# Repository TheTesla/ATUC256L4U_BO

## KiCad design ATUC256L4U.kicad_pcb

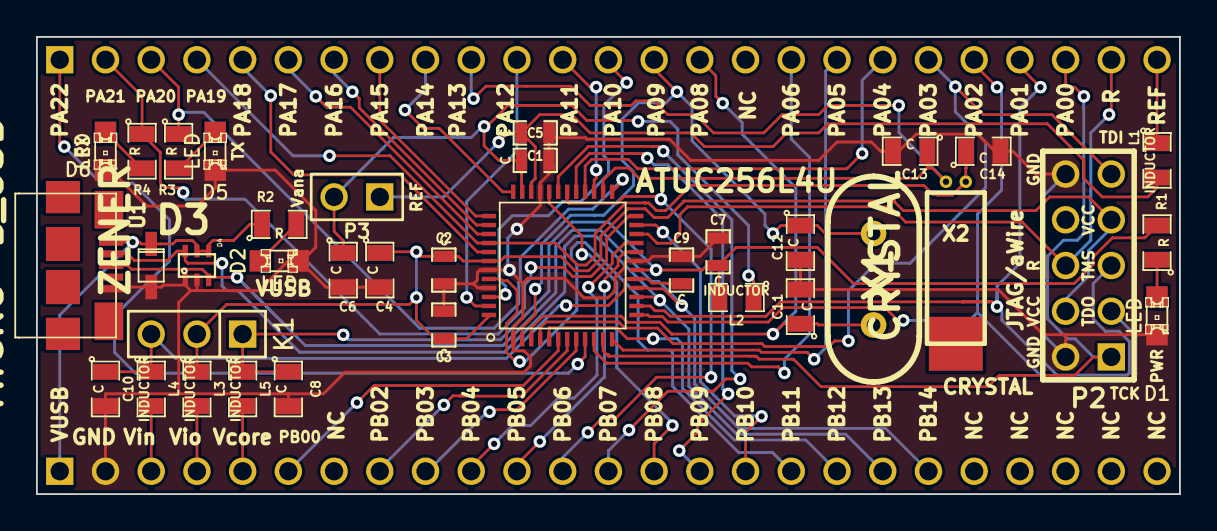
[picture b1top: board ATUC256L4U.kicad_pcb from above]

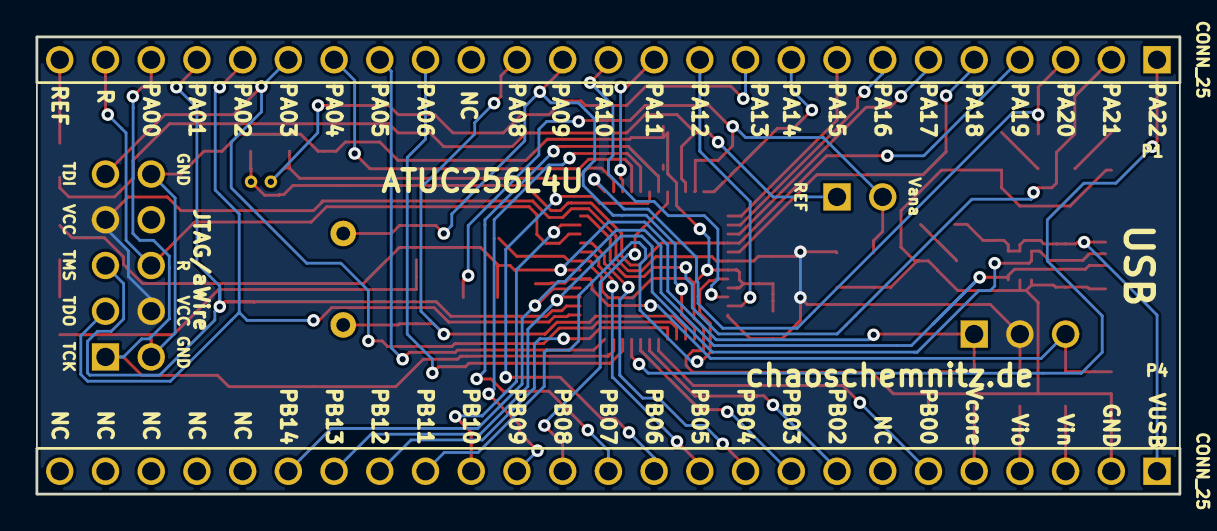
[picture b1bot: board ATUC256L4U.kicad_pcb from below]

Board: 2 copper layers, 63.5 x 25.4 mm, 38 parts (2 on the bottom side), 52 nets.

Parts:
C1, C2, C3, C5, C7, C9: C; SM0603_Capa
C4, C6, C8, C10, C11, C12, C13, C14: C; SM0805
D1, D2, D5, D6: LED; LED-0805
D3: ZENER; SOD323
D4: BAS70BRW; SOT-363
IC1: ATUC256L4U; LQFP48
K1: CONN_3; PIN_ARRAY_3X1
L1, L2, L3, L4, L5: INDUCTOR; SM0805
P1, P4: CONN_25; PIN_ARRAY_25X1
P2: CONN_5X2; PIN_ARRAY_5x2
P3: CONN_2; PIN_ARRAY_2X1
R1, R2, R3, R4: R; SM0805
U1: MICRO-B_USB
X1: CRYSTAL; HC-49V
X2: CRYSTAL; crystal_tc-38_horiz

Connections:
+1.8V: L5.2, P4.5
+3.3V: L4.2, P4.3
+5V: D3.2, D4.4, D4.5, P4.1, R2.1, U1.1
GND: C1.2, C2.2, C3.2, C4.2, C5.2, C6.2, C7.2, C8.2, C9.2, C10.2, C11.2, C12.2, C13.2, C14.2, D1.2, D2.2, D3.1, D4.1, D4.2, D5.2, D6.2, IC1.1, IC1.19, IC1.33, IC1.43, IC1.45, P2.2, P2.10, P4.2, U1.5
unnamed: L1.1, P1.25
unnamed: C1.1, IC1.34, L1.2, P3.1
unnamed: IC1.5, P4.18
unnamed: IC1.44, P4.17
unnamed: IC1.23, P4.16
unnamed: IC1.29, P4.15
unnamed: IC1.32, P4.14
unnamed: IC1.31, P4.13
unnamed: IC1.30, P4.12
unnamed: IC1.20, P4.11
unnamed: IC1.21, P4.10
unnamed: IC1.8, P4.9
unnamed: IC1.7, P4.8
unnamed: IC1.6, P4.6
unnamed: D1.1, R1.1
unnamed: D6.1, R4.2
unnamed: D5.1, R3.2
unnamed: D4.3, IC1.16, P4.20, U1.3
unnamed: D4.6, IC1.15, P4.19, U1.2
unnamed: D2.1, R2.2
unnamed: IC1.4, P1.20, P2.9
unnamed: IC1.22, P1.24, P2.6
unnamed: IC1.14, P1.22, P2.5
unnamed: IC1.13, P1.21, P2.3
unnamed: IC1.11, P1.23, P2.1
unnamed: IC1.25, P1.3, R3.1
unnamed: IC1.24, P1.2, R4.1
unnamed: IC1.12, P1.18
unnamed: IC1.41, P1.5
unnamed: C14.1, IC1.40, P1.4, X2.2
unnamed: IC1.10, P1.17
unnamed: IC1.9, P1.1
unnamed: C11.1, IC1.3, P1.15, X1.1
unnamed: C12.1, IC1.2, P1.14, X1.2
unnamed: IC1.39, P1.6
unnamed: IC1.38, P1.7
unnamed: IC1.28, P1.19
unnamed: IC1.47, P1.11
unnamed: IC1.37, P1.8
unnamed: IC1.27, P1.12
unnamed: IC1.46, P1.13
unnamed: IC1.36, P1.9
unnamed: C13.1, IC1.26, P1.10, X2.1
unnamed: C7.1, C8.1, IC1.18, K1.1, L2.2, L5.1, R1.2
unnamed: C5.1, C6.1, IC1.35, L2.1, P3.2
unnamed: C9.1, C10.1, IC1.17, K1.3, L4.1
VCC: C2.1, C3.1, C4.1, IC1.42, IC1.48, K1.2, L3.1, P2.4, P2.7
VDD: L3.2, P4.4

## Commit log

2013-10-21 Schematic ready, Component-Packages ready, Layout ready
2013-10-22 added some attributes to schematic components
